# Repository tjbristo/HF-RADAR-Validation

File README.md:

# HF-RADAR-data-integration
Code that has been used, also is helpful for different pieces like GNSS fixing and IMU integration. All the code here is used through Arduino IDE with C/C++ programming

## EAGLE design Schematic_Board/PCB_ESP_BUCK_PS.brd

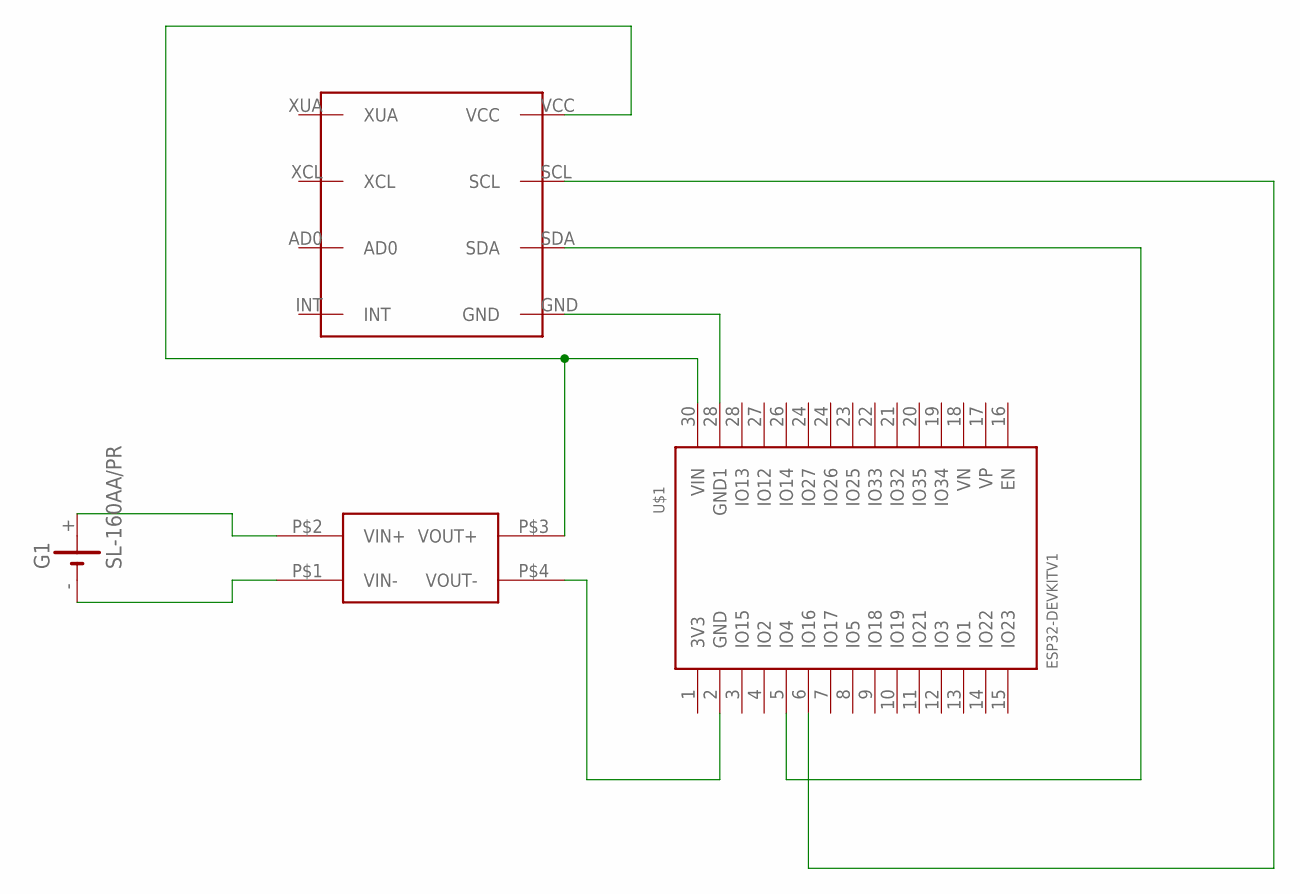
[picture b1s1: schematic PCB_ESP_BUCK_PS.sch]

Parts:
G1: SL-160AA/PR
U$1: ESP32DEVKITV1; ESP32-DEVKITV1
U$2: MP1584-MINI; MINI-DC-BRICK
U$3: MPU-6050

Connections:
unnamed: G1.+, U$2.P$2 (VIN+)
unnamed: G1.-, U$2.P$1 (VIN-)
unnamed: U$1.2 (GND), U$2.P$4 (VOUT-)
unnamed: U$1.30 (VIN), U$2.P$3 (VOUT+), U$3.VCC
unnamed: U$1.28 (IO13), U$3.GND
unnamed: U$1.5 (IO4), U$3.SDA
unnamed: U$1.6 (IO16), U$3.SCL

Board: 2 copper layers, 4 parts (0 on the bottom side), 7 nets, no tracks yet.

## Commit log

2026-03-17 Add files via upload
    Scanner3 checks what address I2C components are on; the I2C scanner checks what addresses the SDA and SCL pins are using. Basic readings are the file for acceleration, rotation, and temperature (whic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
2026-03-18 Create Libraries
2026-03-20 WalterModem Library
2026-03-20 Updated Files
    Restructured the repository with new folders. Added only the code that we are working off of.
2026-03-22 Create EAGLE
2026-03-22 All files
    This has the schematic developed in EAGLE for this project, as well as the PCB board file, I have included the files of the ESP, the IMU, and the LoRa chip too which can be imported into EAGLE
2026-03-22 Add description for HF Radar Validation schematic
2026-03-22 SD card integration
    Added a datasheet of the intended Arduino SD card holder in here, code was updated in the Thingspeak_GNSS_IMU file, make sure to read the abstract at the top of the file.
2026-03-22 Micro SD Card Reader .brd
2026-03-22 Micro SD Card Reader .sch
2026-03-22 Created framework code for IMU information logging
2026-03-22 Added Datasheet
2026-03-23 Data Storage implementation setup/upload rework
    The code is now setup to store IMU data that is ready to be written onto the SD card. In addition the GNSS data is now being stored for 10 minutes before being sent to Thingspeak now using http.
    *This is yet to be fully tested.
